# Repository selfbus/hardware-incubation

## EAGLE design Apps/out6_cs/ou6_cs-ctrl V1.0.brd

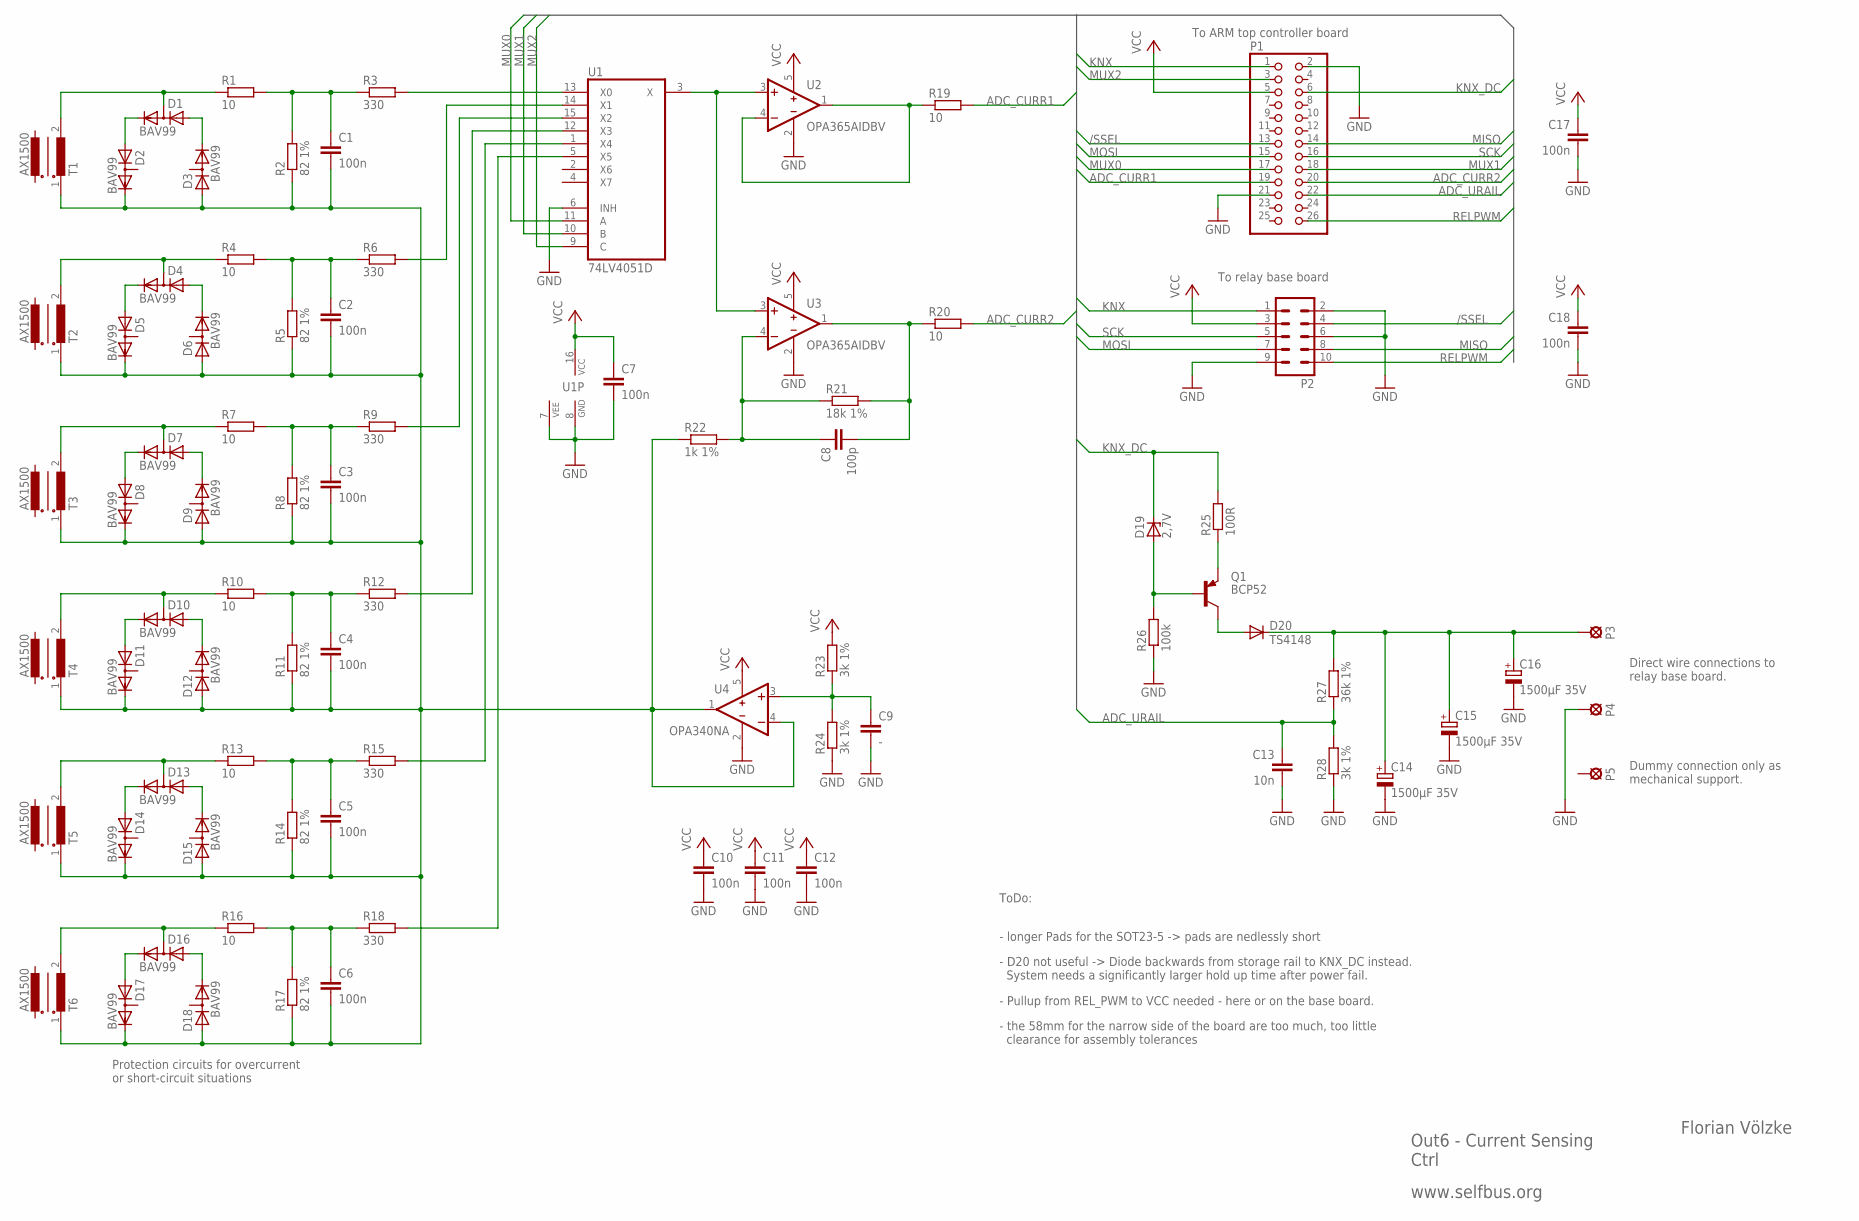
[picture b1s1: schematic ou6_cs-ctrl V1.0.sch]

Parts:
C1, C2, C3, C4, C5, C6, C7, C10, C11, C12, C17, C18: 100n; R0805M
C8: 100p; R0805M
C9: -; R0805M
C13: 10n; R0805M
C14, C15, C16: 1500µF 35V; E5-13-30
D1, D2, D3, D4, D5, D6, D7, D8, D9, D10, D11, D12, D13, D14, D15, D16, D17, D18: BAV99; SOT23
D19: 2,7V; SOT23
D20: TS4148; MINIMELF
P1: PINHD-2X13SMD; 2X13SMD
P2: ML10
P3, P4, P5: SE1.5; SE15
Q1: BCP52; SOT223
R1, R4, R7, R10, R13, R16, R19, R20: 10; R0805M
R2, R5, R8, R11, R14, R17: 82 1%; R0805M
R3, R6, R9, R12, R15, R18: 330; R0805M
R21: 18k 1%; R0805M
R22: 1k 1%; R0805M
R23, R24, R28: 3k 1%; R0805M
R25: 100R; R0805M
R26: 100k; R0805M
R27: 36k 1%; R0805M
T1, T2, T3, T4, T5, T6: AX1500; SMALLXFORMER
U1: 74LV4051D; SO16
U2, U3: OPA365AIDBV; SOT23-5
U4: OPA340NA; SOT23-5

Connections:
/SSEL: P1.13, P2.4
ADC_CURR1: P1.19, R19.2
ADC_CURR2: P1.20, R20.2
ADC_URAIL: C13.1, P1.22, R27.1, R28.2
GND: C7.2, C9.2, C10.2, C11.2, C12.2, C13.2, C14.-, C15.-, C16.-, C17.2, C18.2, P1.2, P1.21, P2.2, P2.6, P2.9, P4.MP, R24.1, R26.1, R28.1, U1.6 (INH), U1.7 (VEE), U1.8 (GND), U2.2 (V-), U3.2 (V-), U4.2 (V-)
KNX: P1.1, P2.1
KNX_DC: D19.3 (C), P1.6, R25.2
MISO: P1.14, P2.8
MOSI: P1.15, P2.7
MUX0: P1.17, U1.11 (A)
MUX1: P1.18, U1.10 (B)
MUX2: P1.3, U1.9 (C)
unnamed: R19.1, U2.1 (OUT), U2.4 (-IN)
unnamed: D1.3 (AC), R1.1, T1.2 (W1E)
unnamed: D1.2 (C), D2.1 (A)
unnamed: D1.1 (A), D3.2 (C)
unnamed: C1.1, R1.2, R2.2, R3.1
unnamed: Q1.3 (E), R25.1
unnamed: D4.3 (AC), R4.1, T2.2 (W1E)
unnamed: D4.2 (C), D5.1 (A)
unnamed: D4.1 (A), D6.2 (C)
unnamed: C2.1, R4.2, R5.2, R6.1
unnamed: C8.2, R20.1, R21.2, U3.1 (OUT)
unnamed: D7.3 (AC), R7.1, T3.2 (W1E)
unnamed: D7.2 (C), D8.1 (A)
unnamed: D7.1 (A), D9.2 (C)
unnamed: C3.1, R7.2, R8.2, R9.1
unnamed: U1.3 (X), U2.3 (+IN), U3.3 (+IN)
unnamed: D10.3 (AC), R10.1, T4.2 (W1E)
unnamed: D10.2 (C), D11.1 (A)
unnamed: D10.1 (A), D12.2 (C)
unnamed: C4.1, R10.2, R11.2, R12.1
unnamed: C8.1, R21.1, R22.2, U3.4 (-IN)
unnamed: D13.3 (AC), R13.1, T5.2 (W1E)
unnamed: D13.2 (C), D14.1 (A)
unnamed: D13.1 (A), D15.2 (C)
unnamed: C5.1, R13.2, R14.2, R15.1
unnamed: C1.2, C2.2, C3.2, C4.2, C5.2, C6.2, D2.2 (C), D3.1 (A), D5.2 (C), D6.1 (A), D8.2 (C), D9.1 (A), D11.2 (C), D12.1 (A), D14.2 (C), D15.1 (A), D17.2 (C), D18.1 (A), R2.1, R5.1, R8.1, R11.1, R14.1, R17.1, R22.1, T1.1 (W1A), T2.1 (W1A), T3.1 (W1A), T4.1 (W1A), T5.1 (W1A), T6.1 (W1A), U4.1 (OUT), U4.4 (-IN)
unnamed: D16.3 (AC), R16.1, T6.2 (W1E)
unnamed: D16.2 (C), D17.1 (A)
unnamed: D16.1 (A), D18.2 (C)
unnamed: C6.1, R16.2, R17.2, R18.1
unnamed: R3.2, U1.13 (X0)
unnamed: R6.2, U1.14 (X1)
unnamed: R9.2, U1.15 (X2)
unnamed: R12.2, U1.12 (X3)
unnamed: R15.2, U1.1 (X4)
unnamed: R18.2, U1.5 (X5)
unnamed: C9.1, R23.1, R24.2, U4.3 (+IN)
unnamed: D20.A, Q1.2 (C), Q1.4 (C)
unnamed: C14.+, C15.+, C16.+, D20.C, P3.MP, R27.2
unnamed: D19.1 (A), Q1.1 (B), R26.2
RELPWM: P1.26, P2.10
SCK: P1.16, P2.5
VCC: C7.1, C10.1, C11.1, C12.1, C17.1, C18.1, P1.5, P2.3, R23.2, U1.16 (VCC), U2.5 (V+), U3.5 (V+), U4.5 (V+)

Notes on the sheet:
Florian Völzke
Out6 - Current Sensing Ctrl
www.selfbus.org
Protection circuits for overcurrent or short-circuit situations
To ARM top controller board
To relay base board
Direct wire connections to relay base board.
Dummy connection only as mechanical support.
ToDo:
- longer Pads for the SOT23-5 -> pads are nedlessly short
- D20 not useful -> Diode backwards from storage rail to KNX_DC instead. System needs a significantly larger hold up time after power fail.
- Pullup from REL_PWM to VCC needed - here or on the base board.
- the 58mm for the narrow side of the board are too much, too little clearance for assembly tolerances

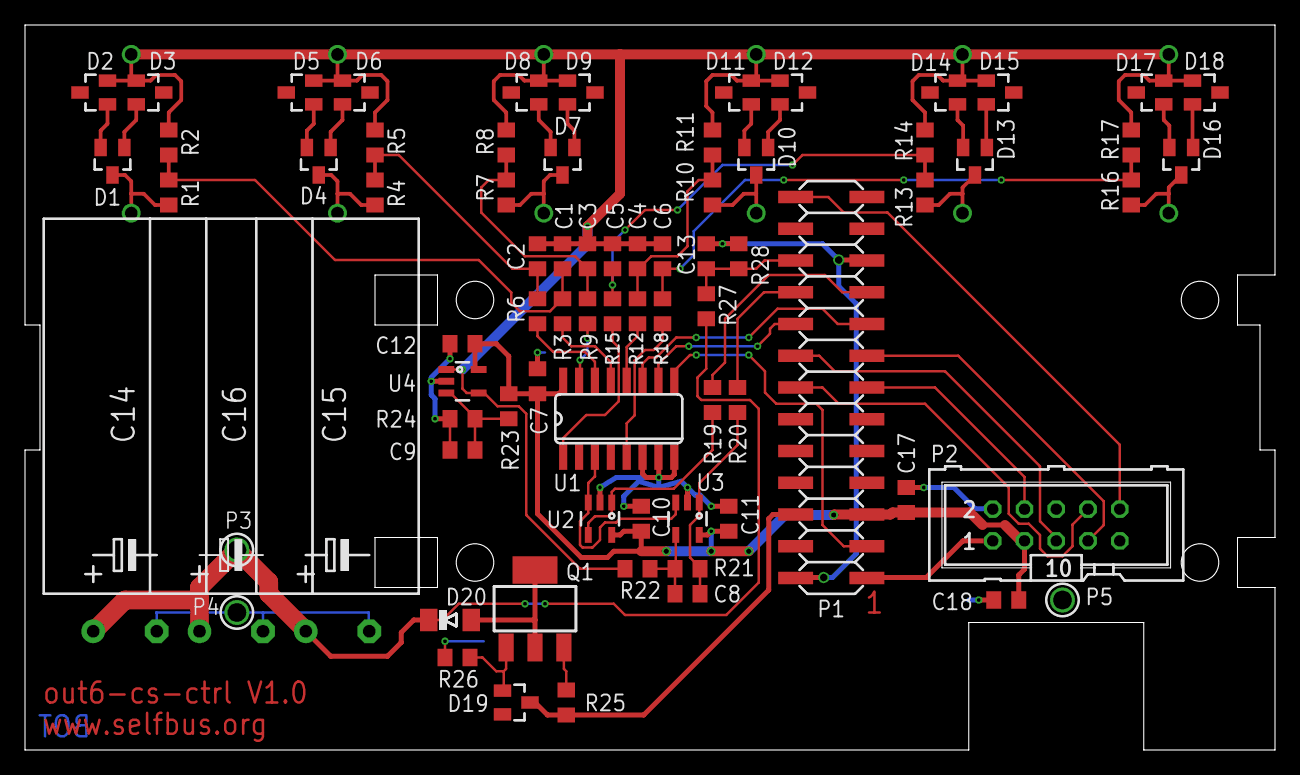
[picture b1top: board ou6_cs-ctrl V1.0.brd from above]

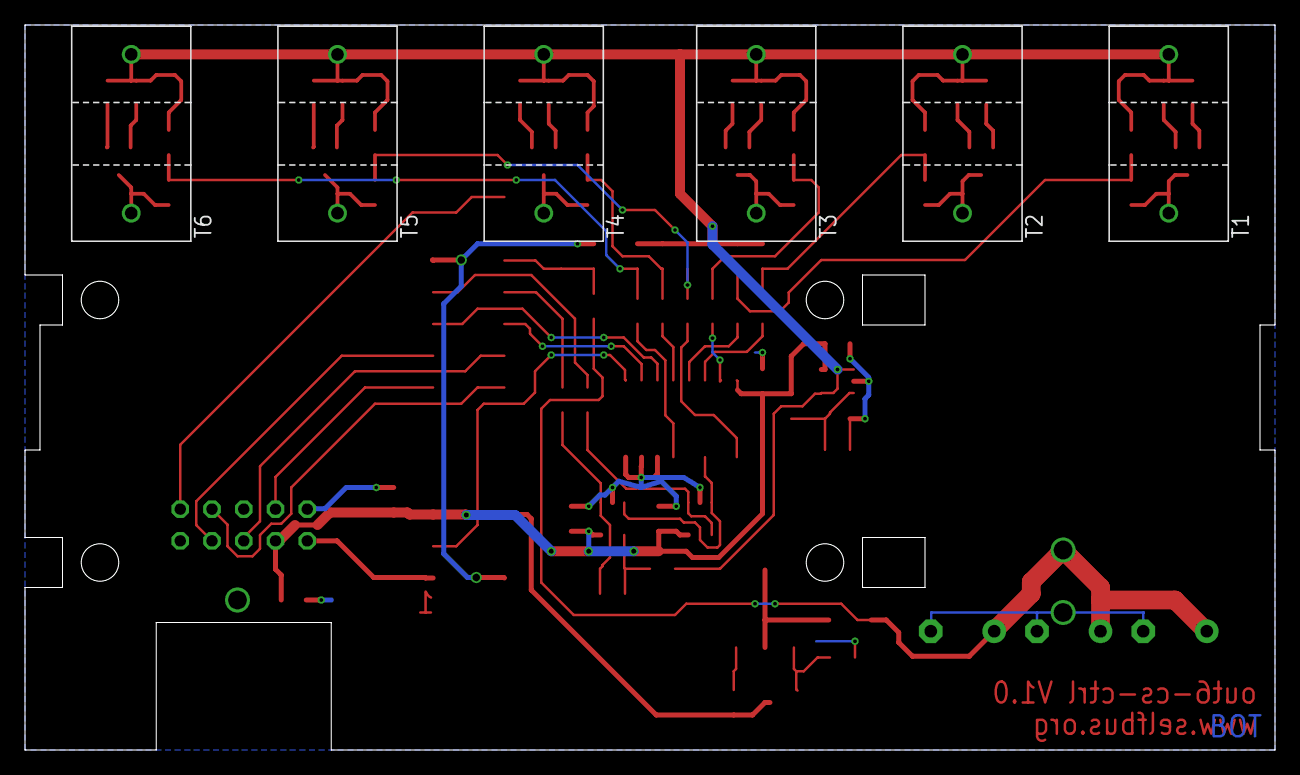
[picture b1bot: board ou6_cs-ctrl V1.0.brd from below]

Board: 2 copper layers, 100.0 x 58.0 mm, 82 parts (6 on the bottom side), 55 nets.

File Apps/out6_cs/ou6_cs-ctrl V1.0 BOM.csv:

"Qty","Value","Package","Parts","Anmerkung","Lieferant","Bestellartikel","Artikelpreis","VPE","Postenpreis",
1,,,"Platine out6-cs-ctrl",,,,,,,
4,,,"Abstandshalter","3D-Druck",,,,,,
1,,,"Wannenstecker 2x5pol 2,54mm",,"Reichelt","WSL 10G","0,09",1,"0,09",
1,,,"Pfostenbuchse 2x5pol 2,54mm","ohne Zugentlastung","Reichelt","PFL 10","0,09",1,"0,09",
1,,,"Pfostenbuchse 2x13pol 2,54mm","ohne Zugentlastung","Reichelt","PFL 26","0,19",1,"0,19",
1,,,"Flachbandkabel 10pol RM1,27","55mm, bzw 48mm Mitte-Mitte Steckverbinder","Reichelt","AWG 28-10G 3M","2,3",30,"0,0766666667",
1,,,"Flachbandkabel 26pol RM1,27","33mm, bzw 27mm Mitte-Mitte Steckverbinder","Reichelt","AWG 28-26G 3M","3,3",30,"0,11",
1,,"2X13SMD","P1","kürzen zu 2x13 Pole","Reichelt","SL 2X20G SMD2,54","1,1",1,"1,1",
8,"10R","R0805","R1, R4, R7, R10, R13, R16, R19, R20","RESISTOR, European symbol","Reichelt","SMD-0805 10,0","0,03",1,"0,24",
6,"82 1%","R0805","R2, R5, R8, R11, R14, R17","RESISTOR, European symbol","Reichelt","SMD-0805 82,0","0,03",1,"0,18",
1,"100R","R0805","R25","RESISTOR, European symbol","Reichelt","SMD-0805 100","0,03",1,"0,03",
6,"330 1%","R0805","R3, R6, R9, R12, R15, R18","RESISTOR, European symbol","Reichelt","SMD-0805 330","0,03",1,"0,18",
1,"1k 1%","R0805","R22","RESISTOR, European symbol","Reichelt","SMD-0805 1,00K","0,03",1,"0,03",
3,"3k 1%","R0805","R23, R24, R28","RESISTOR, European symbol","Reichelt","SMD-0805 3,30K","0,03",1,"0,09",
1,"18k 1%","R0805","R21","RESISTOR, European symbol","Reichelt","SMD-0805 18,0K","0,03",1,"0,03",
1,"36k 1%","R0805","R27","RESISTOR, European symbol","Reichelt","RND 0805 1 36k","0,02",1,"0,02",
1,"100k","R0805","R26","RESISTOR, European symbol","Reichelt","SMD-0805 100K","0,03",1,"0,03",
1,"100p","C0805","C8","CAPACITOR, European symbol","Reichelt","NPO-G0805 100P","0,04",1,"0,04",
12,"100n","C0805","C1, C2, C3, C4, C5, C6, C7, C10, C11, C12, C17, C18","CAPACITOR, European symbol","Reichelt","X7R-G0805 100N","0,04",1,"0,48",
1,"10n","C0805","C13","CAPACITOR, European symbol","Reichelt","X7R-G0805 10N","0,04",1,"0,04",
3,"1500µF 35V","E5-13-30","C14, C15, C16","POLARIZED CAPACITOR, European symbol","Reichelt","RAD FR 1.500/35","0,54",1,"1,62",
1,"2,7V","SOT23","D19","Z-Diode","Reichelt","SMD ZD 2,7","0,04",1,"0,04",
1,"74LV4051D","SOIC-16-N","U1","alternativ: Conrad 1114074 ,1187364","Conrad",1048019,"0,68",1,"0,68","Erstaunlich schlecht zu beziehen"
6,"AX1500","SMALLXFORMER","T1, T2, T3, T4, T5, T6",,"TME","TALEMA AX-1500 ","2,32",1,"13,92",
18,"BAV99","SOT23","D1, D2, D3, D4, D5, D6, D7, D8, D9, D10, D11, D12, D13, D14, D15, D16, D17, D18","2 Diodes - Cathode-Anode|Cathode-Anode","Reichelt","BAV 99 SMD","0,04",1,"0,72",
1,"BCP52","SOT223","Q1","PNP Transistor","Reichelt","BCP 52-16 SMD","0,14",1,"0,14",
1,"OPA340NA","SOT23-5","U4",,"Conrad",1071817,"2,15",1,"2,15",
2,"OPA365AIDBV","SOT23-5","U2, U3",,"Conrad",1071682,"2,12",1,"4,24",
1,"TS4148","MINIMELF","D20","DIODE","Reichelt","TS 4148-1206","0,04",1,"0,04",
,,,,,,,,,,
,,,,,,,,,"27,82 je Baugruppe zzgl Abstandshalter",

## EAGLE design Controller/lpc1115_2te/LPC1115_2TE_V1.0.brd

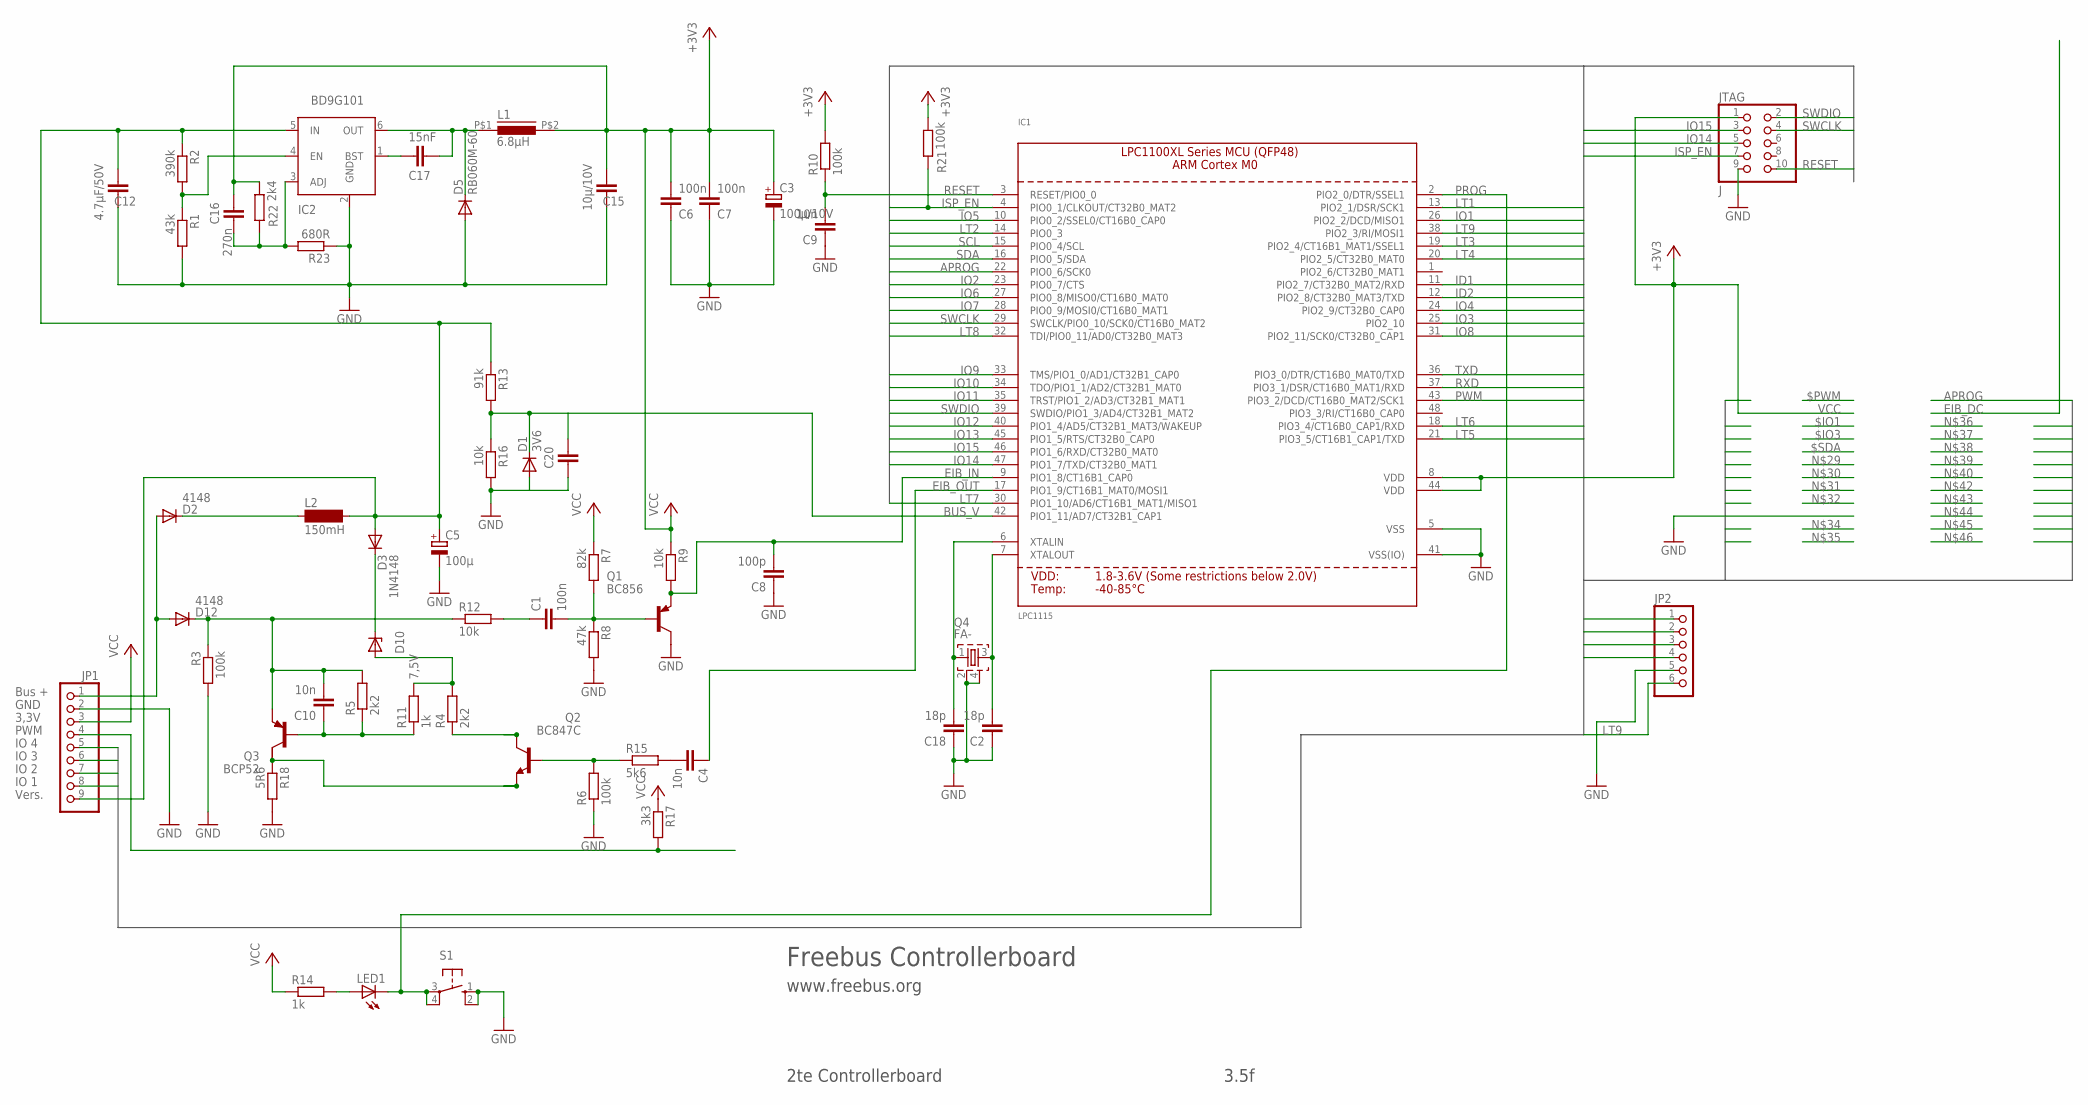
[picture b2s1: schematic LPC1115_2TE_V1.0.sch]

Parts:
C1, C6, C7: 100n; C1206
C2, C18: 18p; C0603
C3: 100µ/10V; E2,5-5
C4, C10: 10n; C1206
C5: 100µ; E3,5-8
C8: 100p; C1206K
C9: 10n; C1206K
C12: 4.7µF/50V; C1206K
C15: 10µ/10V; C1206K
C16: 270n; C1206
C17: 15nF; C1206
C20: C-EUC1206; C1206
D1: 3V6; MINIMELF
D2, D12: 4148; MINIMELF
D3: 1N4148; MINIMELF
D5: RB060M-60; SOD123
D10: 7,5V; MINIMELF
IC1: LPC1115; LQFP48
IC2: BD9G101; SOT23-6
JP1: PINHD-1X9; 1X09
JP2: PINHD-1X6; 1X06
JTAG: J; 2X05M
L1: 6.8µH; PIS2812
L2: 150mH; BS11
LED1: LED3MM
Q1: BC856; SOT23-BEC
Q2: BC847C; SOT23
Q3: BCP52; SOT223
Q4: FA-; ASE
R1: 43k; R1206
R2: 390k; R1206
R3, R6, R10, R21: 100k; R1206
R4, R5: 2k2; R1206
R7: 82k; R1206
R8: 47k; R1206
R9, R12, R16: 10k; R1206
R11, R14: 1k; R1206
R13: 91k; R1206
R15: 5k6; R1206
R17: 3k3; R1206
R18: 5R6; R1206
R22: 2k4; R1206
R23: 680R; R1206
S1: 10-XX; B3F-10XX

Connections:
APROG: IC1.22 (PIO0_6/SCK0), JP1.8
BASE: C1.2, Q1.B, R7.2, R8.1
BASE_SEND: Q2.1 (B), R6.2, R15.1
BUS_V: C20.2, D1.C, IC1.42 (PIO1_11/AD7/CT32B1_CAP1), R13.2, R16.1
EIB+: D2.A, D12.A, JP1.1
EIB_DC: C5.+, C12.2, D3.A, IC2.5 (IN), JP1.9, L2.2, R2.1, R13.1
EIB_IN: C8.2, IC1.9 (PIO1_8/CT16B1_CAP0), Q1.E, R9.2
EIB_OUT: C4.1, IC1.17 (PIO1_9/CT16B1_MAT0/MOSI1)
GND: C2.1, C3.-, C5.-, C6.1, C7.1, C8.1, C9.1, C12.1, C15.1, C18.1, C20.1, D1.A, D5.A, IC1.5 (VSS), IC1.41 (VSS(IO)), IC2.2 (GND), JP1.2, JP2.5, JTAG.9, Q1.C, Q4.2, Q4.4, R1.2, R3.2, R6.1, R8.2, R16.2, R18.2, R23.1, S1.1 (S), S1.2 (S1)
ID1: IC1.11 (PIO2_7/CT32B0_MAT2/RXD)
ID2: IC1.12 (PIO2_8/CT32B0_MAT3/TXD)
IO1: IC1.26 (PIO2_2/DCD/MISO1)
IO2: IC1.23 (PIO0_7/CTS)
IO3: IC1.25 (PIO2_10)
IO4: IC1.24 (PIO2_9/CT32B0_CAP0), JP1.5
IO5: IC1.10 (PIO0_2/SSEL0/CT16B0_CAP0)
IO6: IC1.27 (PIO0_8/MISO0/CT16B0_MAT0)
IO7: IC1.28 (PIO0_9/MOSI0/CT16B0_MAT1), JP1.7
IO8: IC1.31 (PIO2_11/SCK0/CT32B0_CAP1), JP1.6
IO9: IC1.33 (TMS/PIO1_0/AD1/CT32B1_CAP0)
IO10: IC1.34 (TDO/PIO1_1/AD2/CT32B1_MAT0)
IO11: IC1.35 (TRST/PIO1_2/AD3/CT32B1_MAT1)
IO12: IC1.40 (PIO1_4/AD5/CT32B1_MAT3/WAKEUP)
IO13: IC1.45 (PIO1_5/RTS/CT32B0_CAP0)
IO14: IC1.47 (PIO1_7/TXD/CT32B0_MAT1), JTAG.5
IO15: IC1.46 (PIO1_6/RXD/CT32B0_MAT0), JTAG.3
ISP_EN: IC1.4 (PIO0_1/CLKOUT/CT32B0_MAT2), JTAG.7, R21.1
I_SENSE: Q2.2 (E), Q3.2 (C), R18.1
LT1: IC1.13 (PIO2_1/DSR/SCK1)
LT2: IC1.14 (PIO0_3)
LT3: IC1.19 (PIO2_4/CT16B1_MAT1/SSEL1)
LT4: IC1.20 (PIO2_5/CT32B0_MAT0)
LT5: IC1.21 (PIO3_5/CT16B1_CAP1/TXD), JP2.1
LT6: IC1.18 (PIO3_4/CT16B0_CAP1/RXD), JP2.2
LT7: IC1.30 (PIO1_10/AD6/CT16B1_MAT1/MISO1), JP2.3
LT8: IC1.32 (TDI/PIO0_11/AD0/CT32B0_MAT3), JP2.4
LT9: IC1.38 (PIO2_3/RI/MOSI1), JP2.6
LX: C17.1, D5.C, IC2.6 (OUT), L1.P$1 (1)
unnamed: Q2.3 (C), R4.1
unnamed: C18.2, IC1.6 (XTALIN), Q4.1
unnamed: C2.2, IC1.7 (XTALOUT), Q4.3
unnamed: C10.2, D12.C, Q3.3 (E), R3.1, R5.2, R12.1
unnamed: LED1.A, R14.2
unnamed: D2.C, L2.1
unnamed: D3.C, D10.C
unnamed: C1.1, R12.2
unnamed: C4.2, R15.2
unnamed: C17.2, IC2.1 (BST)
unnamed: IC2.4 (EN), R1.1, R2.2
unnamed: C16.1, IC2.3 (ADJ), R22.1, R23.2
unnamed: C10.1, Q3.1 (B), R5.1, R11.1
PROG: IC1.2 (PIO2_0/DTR/SSEL1), LED1.K (C), S1.3, S1.4 (P1)
PWM: IC1.43 (PIO3_2/DCD/CT16B0_MAT2/SCK1), JP1.4, R17.2
REFERENZ: D10.A, R4.2, R11.2
RESET: C9.2, IC1.3 (RESET/PIO0_0), JTAG.10, R10.1
RXD: IC1.37 (PIO3_1/DSR/CT16B0_MAT1/RXD)
SCL: IC1.15 (PIO0_4/SCL)
SDA: IC1.16 (PIO0_5/SDA)
SWCLK: IC1.29 (SWCLK/PIO0_10/SCK0/CT16B0_MAT2), JTAG.4
SWDIO: IC1.39 (SWDIO/PIO1_3/AD4/CT32B1_MAT2), JTAG.2
TXD: IC1.36 (PIO3_0/DTR/CT16B0_MAT0/TXD)
VCC: C3.+, C6.2, C7.2, C15.2, C16.2, IC1.8 (VDD), IC1.44 (VDD), JP1.3, JTAG.1, L1.P$2 (2), R7.1, R9.1, R10.2, R14.1, R17.1, R21.2, R22.2

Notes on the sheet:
Bus +
GND
3,3V
PWM
IO 1
IO 2
IO 3
IO 4
Vers.
Freebus Controllerboard
www.freebus.org
2te Controllerboard
3.5f

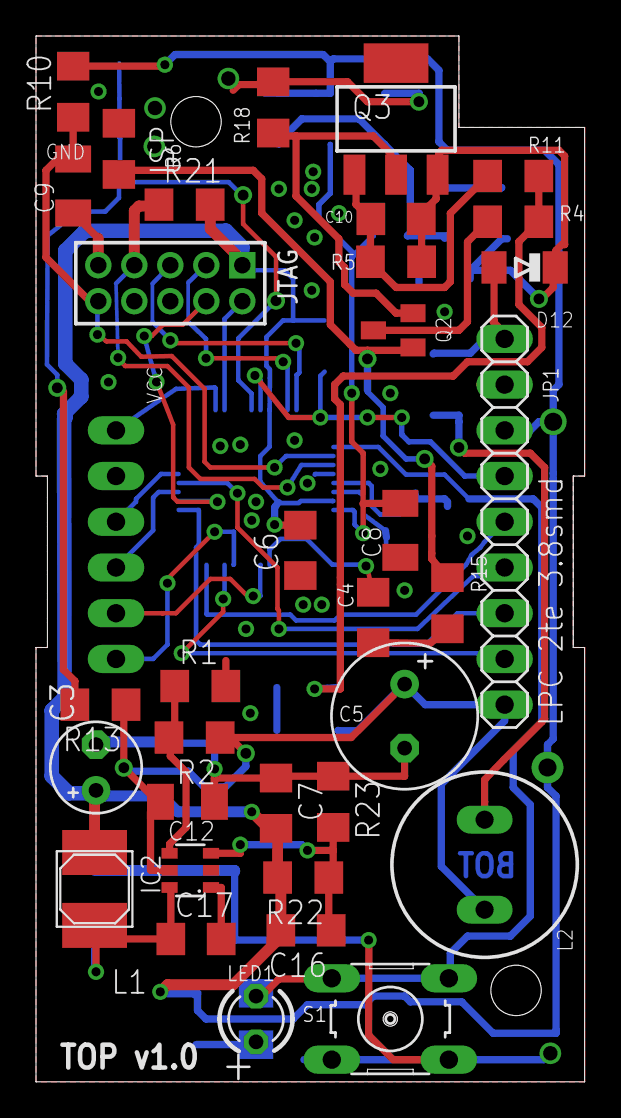
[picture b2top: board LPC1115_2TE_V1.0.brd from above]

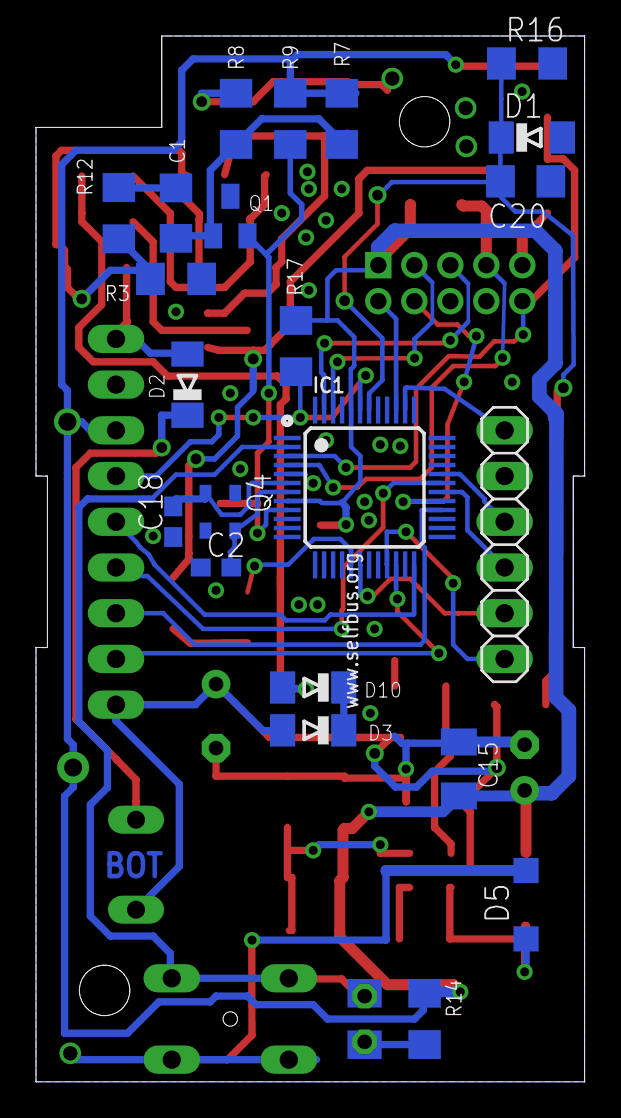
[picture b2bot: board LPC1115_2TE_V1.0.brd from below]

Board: 2 copper layers, 30.5 x 58.1 mm, 56 parts (22 on the bottom side), 42 nets.

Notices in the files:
parts and their libraries:
microbuilder: This work is placed in the public domain, and may be freely used for commercial and non-commercial work with the following conditions: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
